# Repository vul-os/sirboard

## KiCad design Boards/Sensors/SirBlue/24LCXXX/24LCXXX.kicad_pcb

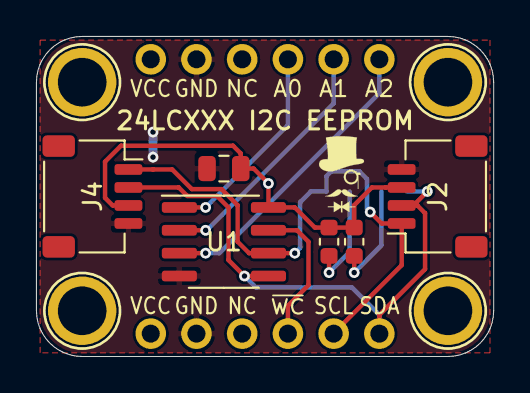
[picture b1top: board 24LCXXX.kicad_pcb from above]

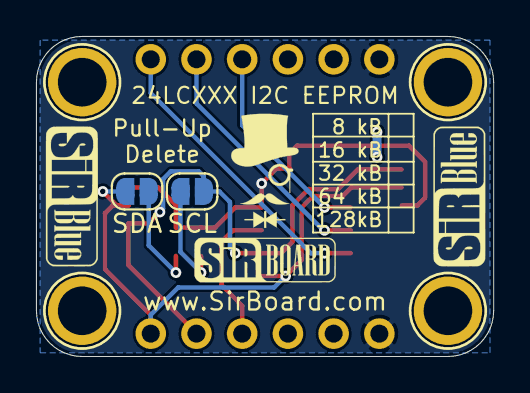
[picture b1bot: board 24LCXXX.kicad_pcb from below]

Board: 2 copper layers, 25.4 x 17.8 mm, 14 parts (4 on the bottom side), 10 nets.

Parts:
C1: 10uF; C_0805_2012Metric
H1, H2, H3, H4: MountingHole; MountingHole_M2.5_SirBoard
J1, J3: Conn_01x06; PinHeader_1x06_P2.54mm_Vertical
J2, J4: Conn_01x04; JST_SH_SM04B-SRSS-TB_1x04-1MP_P1.00mm_Horizontal
R1, R2: 10K; R_0603_1608Metric
SCL: SolderJumper_2_Open; SolderJumper-2_P1.3mm_Open_RoundedPad1.0x1.5mm
SDA: SolderJumper_2_Open; SolderJumper-2_P1.3mm_Open_RoundedPad1.0x1.5mm
U1: 24LC512; SOIC-8_3.9x4.9mm_P1.27mm

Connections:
#WC: J1.4, U1.7
A0: J3.4, U1.1
A1: J3.5, U1.2
A2: J3.6, U1.3
GND: C1.2, J1.2, J2.4, J3.2, J4.4, U1.4
unnamed: R1.2, SDA.2
unnamed: R2.2, SCL.2
SCL: J1.5, J2.1, J4.1, SCL.1, U1.6
SDA: J1.6, J2.2, J4.2, SDA.1, U1.5
VCC: C1.1, J1.1, J2.3, J3.1, J4.3, R1.1, R2.1, U1.8

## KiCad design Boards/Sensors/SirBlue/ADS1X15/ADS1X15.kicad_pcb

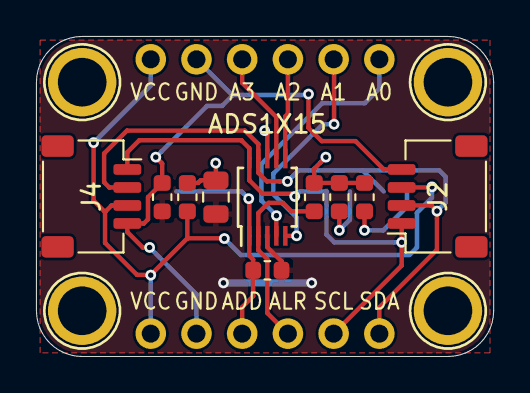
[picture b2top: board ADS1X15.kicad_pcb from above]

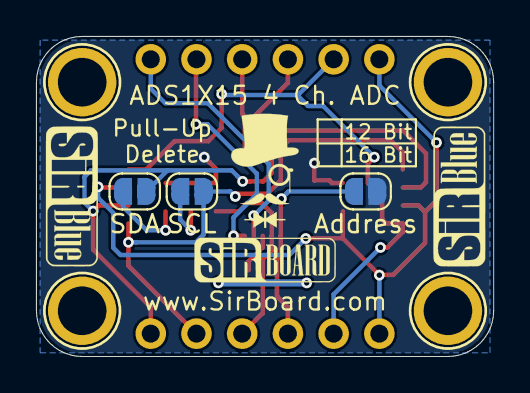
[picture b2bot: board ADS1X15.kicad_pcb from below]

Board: 2 copper layers, 25.4 x 17.8 mm, 19 parts (5 on the bottom side), 14 nets.

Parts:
ADS1X15: ADS1X15; TSSOP-10_3x3mm_P0.5mm
Address: SolderJumper_2_Open; SolderJumper-2_P1.3mm_Open_RoundedPad1.0x1.5mm
C1: 10uF; C_0805_2012Metric
FB1, FB2: Ferrite_Bead; L_0603_1608Metric
H1, H2, H3, H4: MountingHole; MountingHole_M2.5_SirBoard
J1, J3: Conn_01x06; PinHeader_1x06_P2.54mm_Vertical
J2, J4: Conn_01x04; JST_SH_SM04B-SRSS-TB_1x04-1MP_P1.00mm_Horizontal
R1, R2, R3, R4: 10K; R_0603_1608Metric
SCL: SolderJumper_2_Open; SolderJumper-2_P1.3mm_Open_RoundedPad1.0x1.5mm
SDA: SolderJumper_2_Open; SolderJumper-2_P1.3mm_Open_RoundedPad1.0x1.5mm

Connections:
ADDRESS: ADS1X15.1, Address.2, J1.3, R4.1
ALERT: ADS1X15.2, J1.4, R3.2
Ain0: ADS1X15.4, J3.6
Ain1: ADS1X15.5, J3.5
Ain2: ADS1X15.6, J3.4
Ain3: ADS1X15.7, J3.3
GND: FB2.1, J1.2, J2.4, J3.2, J4.4
GND_B: ADS1X15.3, C1.2, FB2.2, R4.2
unnamed: R1.2, SCL.2
unnamed: R2.2, SDA.2
SCL: ADS1X15.10, J1.5, J2.1, J4.1, SCL.1
SDA: ADS1X15.9, J1.6, J2.2, J4.2, SDA.1
VCC: FB1.1, J1.1, J2.3, J3.1, J4.3
VCC_B: ADS1X15.8, Address.1, C1.1, FB1.2, R1.1, R2.1, R3.1

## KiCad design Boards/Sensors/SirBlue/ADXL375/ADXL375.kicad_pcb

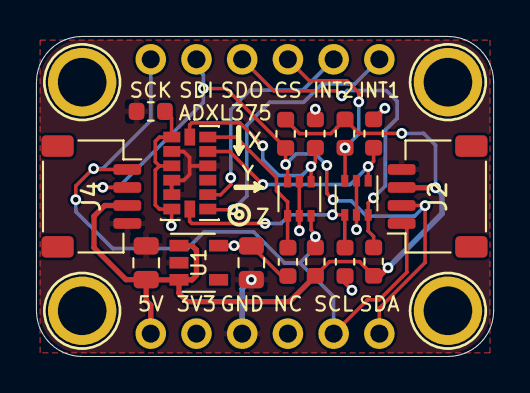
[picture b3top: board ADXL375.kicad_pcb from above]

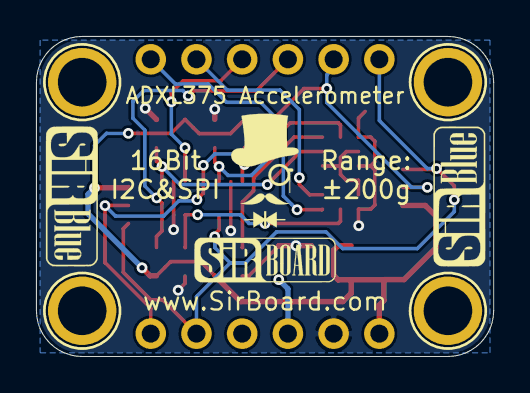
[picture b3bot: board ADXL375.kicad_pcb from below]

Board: 2 copper layers, 25.4 x 17.8 mm, 23 parts (2 on the bottom side), 13 nets.

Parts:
ADXL375: ADXL345; LGA-14_3x5mm_P0.8mm_LayoutBorder1x6y
C1, C4: 10uF; C_0805_2012Metric
C2: 100nF; C_0603_1608Metric
H1, H2, H3, H4: MountingHole; MountingHole_M2.5_SirBoard
J1, J3: Conn_01x06; PinHeader_1x06_P2.54mm_Vertical
J2, J4: Conn_01x04; JST_SH_SM04B-SRSS-TB_1x04-1MP_P1.00mm_Horizontal
Q1, Q2: BSS138DW; SOT-363_SC-70-6
R1, R2, R3, R4, R5, R6, R7, R8: 10K; R_0603_1608Metric
U1: AP2127K-3.3; SOT-23-5

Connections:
3V3: ADXL375.1, ADXL375.3, ADXL375.6, C2.1, C4.1, J1.2, Q1.2, Q1.5, Q2.2, Q2.5, R1.2, R3.2, R5.2, R7.2, U1.5
5V: C1.1, J1.1, J2.3, J4.3, R2.1, R4.1, R6.1, R8.1, U1.1, U1.3
CS_3V3: ADXL375.7, Q1.4, R3.1
CS_5V: J3.4, Q1.3, R4.2
GND: ADXL375.2, ADXL375.4, ADXL375.5, ADXL375.11, C1.2, C2.2, C4.2, J1.3, J2.4, J4.4, U1.2
INT1: ADXL375.8, J3.6
INT2: ADXL375.9, J3.5
SCL_3V3: ADXL375.14, Q2.1, R5.1
SCL_5V: J1.5, J2.1, J3.1, J4.1, Q2.6, R6.2
SDA_3V3: ADXL375.13, Q2.4, R7.1
SDA_5V: J1.6, J2.2, J3.2, J4.2, Q2.3, R8.2
SDO_3V3: ADXL375.12, Q1.1, R1.1
SDO_5V: J3.3, Q1.6, R2.2

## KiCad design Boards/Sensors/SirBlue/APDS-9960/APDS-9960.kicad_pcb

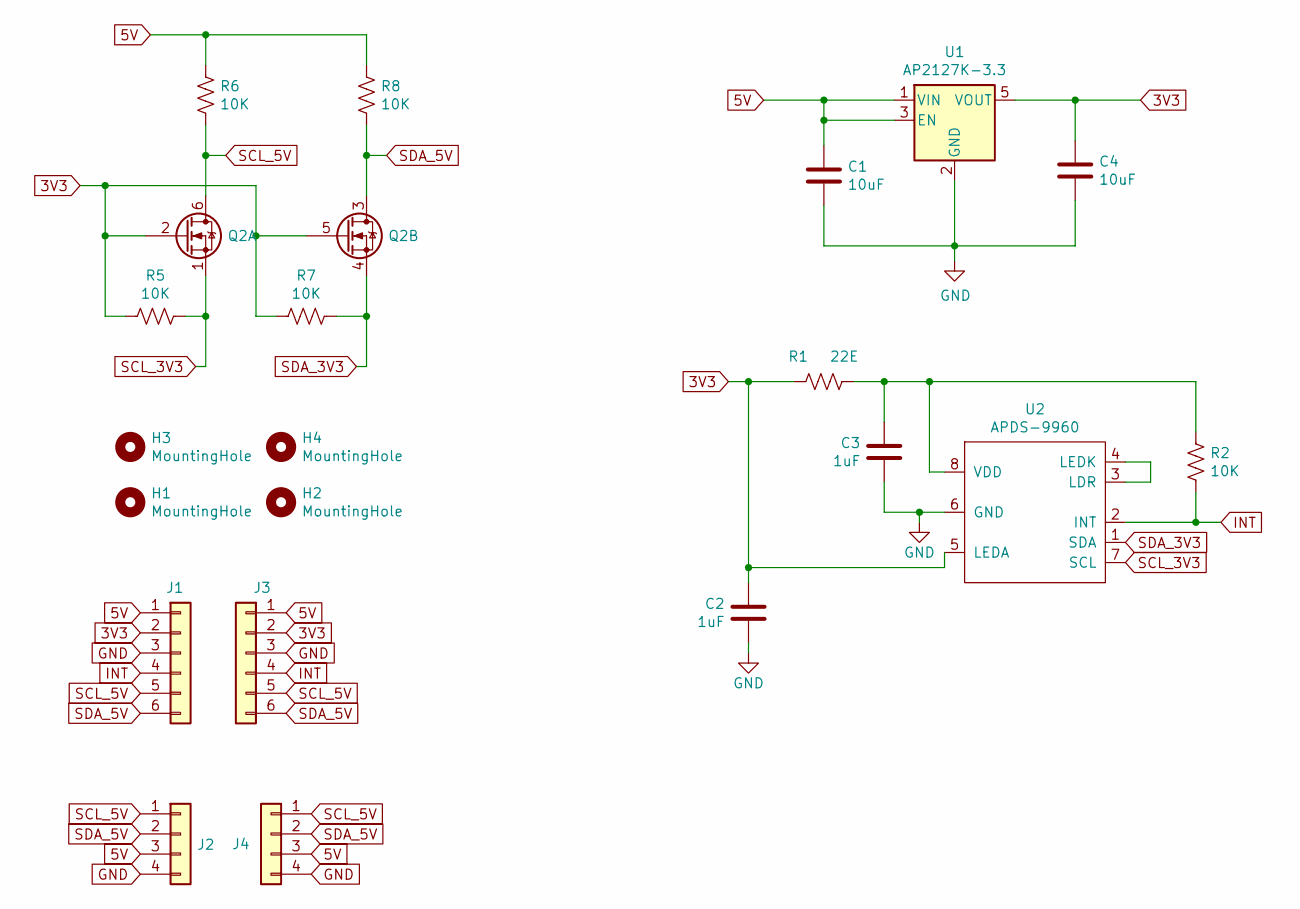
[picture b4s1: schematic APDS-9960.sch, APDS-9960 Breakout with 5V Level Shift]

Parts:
C1, C4: 10uF; C_0805_2012Metric; Part C95841
C2, C3: 1uF; C_0805_2012Metric; Part C396719
H1, H2, H3, H4: MountingHole; MountingHole_M2.5_SirBoard
J1, J3: Conn_01x06; PinHeader_1x06_P2.54mm_Vertical
J2, J4: Conn_01x04; SirBlue_Connector; Part C160404
Q2: BSS138DW; SOT-363_SC-70-6
R1: 22E; R_0603_1608Metric; Part C269708
R2, R5, R6, R7, R8: 10K; R_0603_1608Metric; Part C99198
U1: AP2127K-3.3; SOT-23-5; Part C156285
U2: APDS-9960; DFN8_2.4mmX4mm_P=0.72; Part C93222

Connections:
3V3: C2.1, C4.1, J1.2, J3.2, Q2.2 (G), Q2.5 (G), R1.1, R5.2, R7.2, U1.5 (VOUT), U2.5 (LEDA)
5V: C1.1, J1.1, J2.3, J3.1, J4.3, R6.1, R8.1, U1.1 (VIN), U1.3 (EN)
GND: C1.2, C2.2, C3.2, C4.2, J1.3, J2.4, J3.3, J4.4, U1.2 (GND), U2.6 (GND)
INT: J1.4, J3.4, R2.2, U2.2 (INT)
unnamed: C3.1, R1.2, R2.1, U2.8 (VDD)
unnamed: U2.3 (LDR), U2.4 (LEDK)
SCL_3V3: Q2.1 (S), R5.1, U2.7 (SCL)
SCL_5V: J1.5, J2.1, J3.5, J4.1, Q2.6 (D), R6.2
SDA_3V3: Q2.4 (S), R7.1, U2.1 (SDA)
SDA_5V: J1.6, J2.2, J3.6, J4.2, Q2.3 (D), R8.2

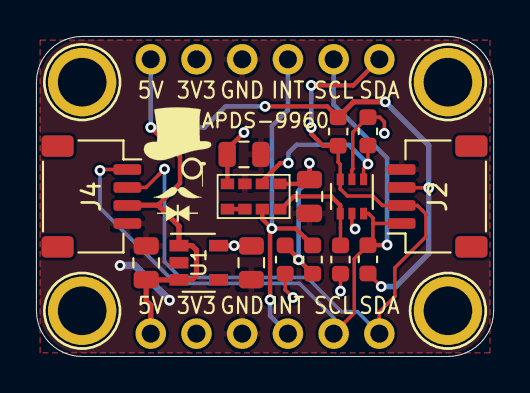
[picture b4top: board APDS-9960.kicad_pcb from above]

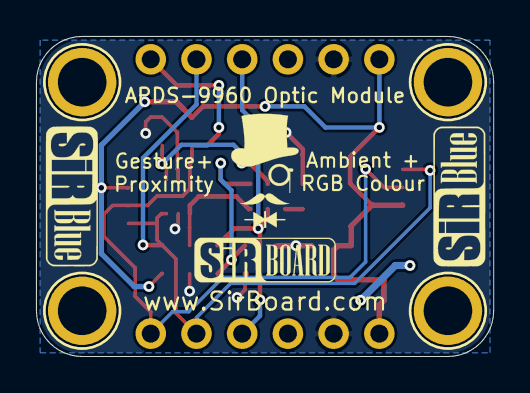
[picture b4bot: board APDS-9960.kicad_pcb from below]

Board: 2 copper layers, 25.4 x 17.8 mm, 21 parts (2 on the bottom side), 10 nets.

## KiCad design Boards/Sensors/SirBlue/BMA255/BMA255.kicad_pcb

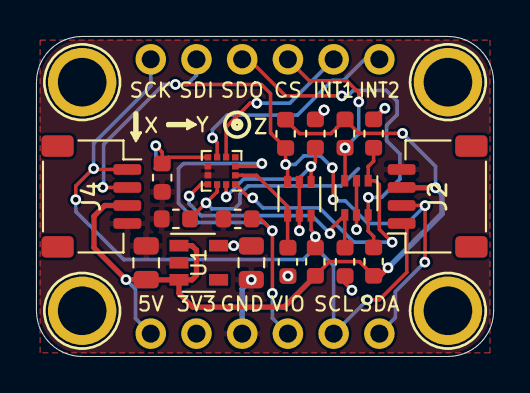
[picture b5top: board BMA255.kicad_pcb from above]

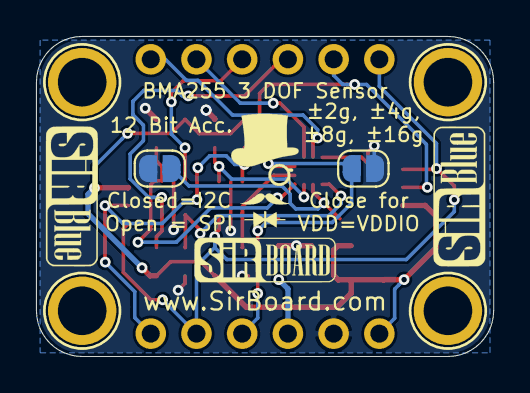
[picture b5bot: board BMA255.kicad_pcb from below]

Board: 2 copper layers, 25.4 x 17.8 mm, 27 parts (4 on the bottom side), 15 nets.

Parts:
C1, C4: 10uF; C_0805_2012Metric
C3: 1uF; C_0603_1608Metric
C5: 100nF; C_0603_1608Metric
H1, H2, H3, H4: MountingHole; MountingHole_M2.5_SirBoard
J1, J3: Conn_01x06; PinHeader_1x06_P2.54mm_Vertical
J2, J4: Conn_01x04; JST_SH_SM04B-SRSS-TB_1x04-1MP_P1.00mm_Horizontal
JP1, JP2: SolderJumper_2_Open; SolderJumper-2_P1.3mm_Open_RoundedPad1.0x1.5mm
Q1, Q2: BSS138DW; SOT-363_SC-70-6
R1, R2, R3, R4, R5, R6, R7, R8, R9: 10K; R_0603_1608Metric
U1: AP2127K-3.3; SOT-23-5
U2: BMA255; LGA-12_2x2mm_P0.5mm

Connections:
3V3: C3.1, C4.1, J1.2, JP1.1, JP2.2, Q1.2, Q1.5, Q2.2, Q2.5, R1.2, R3.2, R5.2, R7.2, U1.5, U2.7
5V: C1.1, J1.1, J2.3, J4.3, R2.1, R4.1, R6.1, R8.1, U1.1, U1.3
CS_3V3: Q1.4, R3.1, U2.10
CS_5V: J3.4, Q1.3, R4.2
GND: C1.2, C3.2, C4.2, C5.2, J1.3, J2.4, J4.4, R9.2, U1.2, U2.8, U2.9
INT1: J3.5, U2.5
INT2: J3.6, U2.6
unnamed: JP2.1, R9.1, U2.11
SCL_3V3: Q2.1, R5.1, U2.12
SCL_5V: J1.5, J2.1, J3.1, J4.1, Q2.6, R6.2
SDA_3V3: Q2.4, R7.1, U2.2
SDA_5V: J1.6, J2.2, J3.2, J4.2, Q2.3, R8.2
SDO_3V3: Q1.1, R1.1, U2.1
SDO_5V: J3.3, Q1.6, R2.2
VDDIO: C5.1, J1.4, JP1.2, U2.3

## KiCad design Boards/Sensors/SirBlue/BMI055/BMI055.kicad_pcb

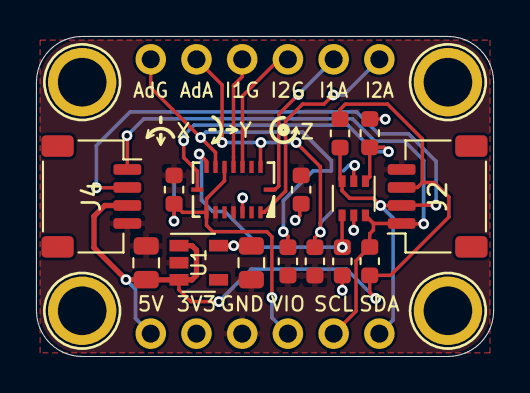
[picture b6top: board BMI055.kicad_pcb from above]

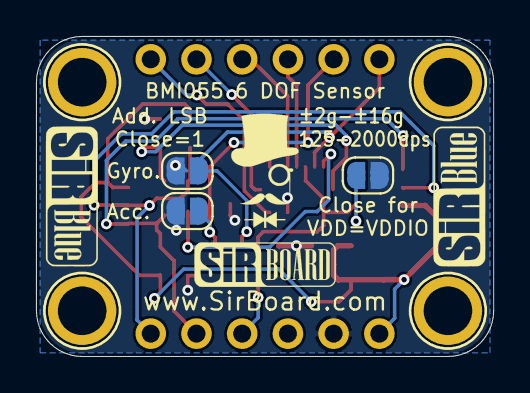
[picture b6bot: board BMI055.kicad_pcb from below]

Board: 2 copper layers, 25.4 x 17.8 mm, 24 parts (5 on the bottom side), 14 nets.

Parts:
C1, C4: 10uF; C_0805_2012Metric
C3: 1uF; C_0603_1608Metric
C5: 100nF; C_0603_1608Metric
H1, H2, H3, H4: MountingHole; MountingHole_M2.5_SirBoard
J1, J3: Conn_01x06; PinHeader_1x06_P2.54mm_Vertical
J2, J4: Conn_01x04; JST_SH_SM04B-SRSS-TB_1x04-1MP_P1.00mm_Horizontal
JP1, JP2, JP3: SolderJumper_2_Open; SolderJumper-2_P1.3mm_Open_RoundedPad1.0x1.5mm
Q2: BSS138DW; SOT-363_SC-70-6
R1, R2, R5, R6, R7, R8: 10K; R_0603_1608Metric
U1: AP2127K-3.3; SOT-23-5
U2: BMI055

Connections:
3V3: C3.1, C4.1, J1.2, JP1.1, JP2.1, JP3.1, Q2.2, Q2.5, R5.2, R7.2, U1.5, U2.3
5V: C1.1, J1.1, J2.3, J4.3, R6.1, R8.1, U1.1, U1.3
A_LSB_A: J3.2, JP2.2, R2.1, U2.15
A_LSB_G: J3.1, JP3.2, R1.1, U2.10
GND: C1.2, C3.2, C4.2, C5.2, J1.3, J2.4, J4.4, R1.2, R2.2, U1.2, U2.4, U2.6
I1A: J3.5, U2.16
I1G: J3.3, U2.12
I2A: J3.6, U2.1
I2G: J3.4, U2.13
SCL_3V3: Q2.1, R5.1, U2.8
SCL_5V: J1.5, J2.1, J4.1, Q2.6, R6.2
SDA_3V3: Q2.4, R7.1, U2.9
SDA_5V: J1.6, J2.2, J4.2, Q2.3, R8.2
VDDIO: C5.1, J1.4, JP1.2, U2.7, U2.11
